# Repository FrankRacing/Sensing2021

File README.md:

# Olin Baja Electrical 2021

This repository contains the hardware, firmware, software, and important technical documents for the 2021 iteration of Olin College of Engineering's Baja project team.

## Repository structure

- hardware: boards 
- packages: store
- parts: COTs 

## Instructions to commit:

The main branch is protected, so you cannot commit directly! You need to make a branch first. We suggest learning how to use VSCode's Version Control tab and installing the GitLens extension.

- Make sure your main branch is up to date (git pull)
- Make sure you're on the main branch
- Call `git checkout -b <your initials>/<branch_name>` 
  - IE for me it would be `git checkout -b jk/important_feature`
- Work on your code, committing frequently
- Push your code to Github
- Make a pull request with your branch
- Wait for your code to be reviewed, responding to review requests
- Merge your branch, and then delete it.

This process will need to be repeated for every change you want to make to the main repository

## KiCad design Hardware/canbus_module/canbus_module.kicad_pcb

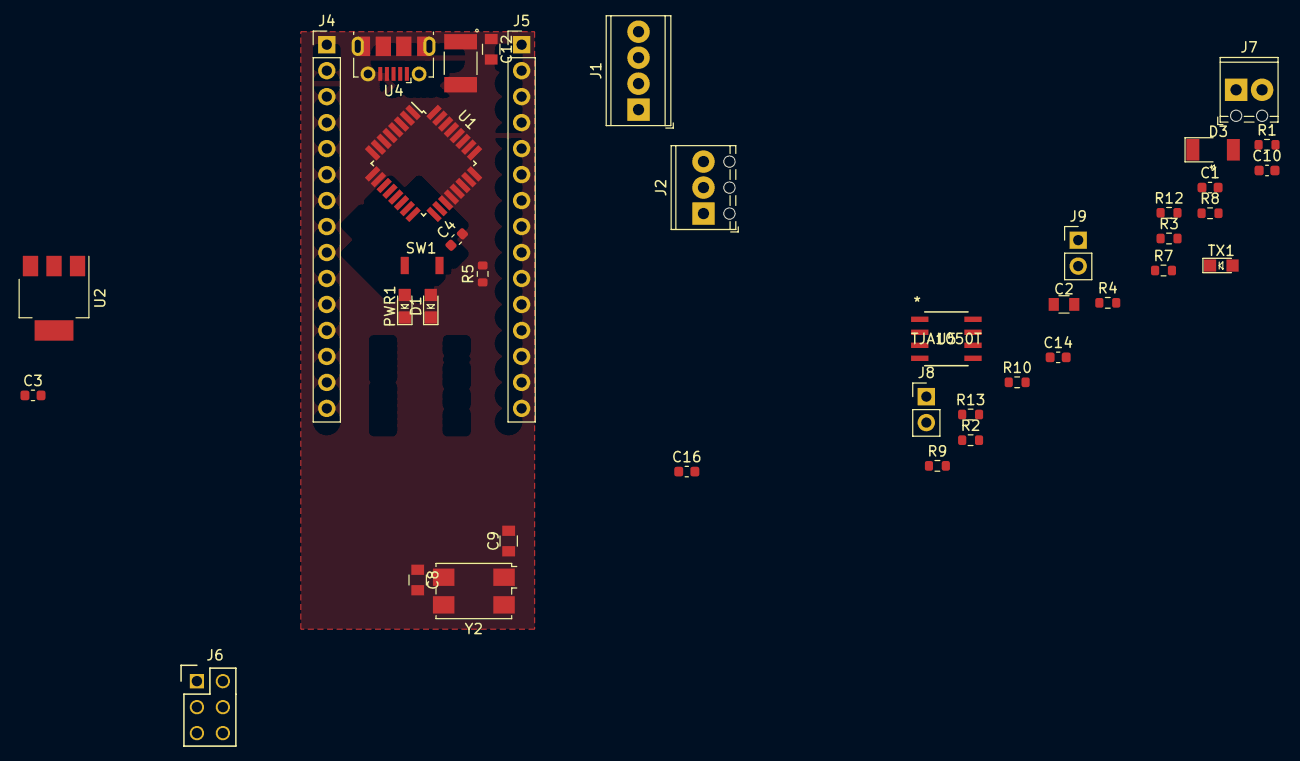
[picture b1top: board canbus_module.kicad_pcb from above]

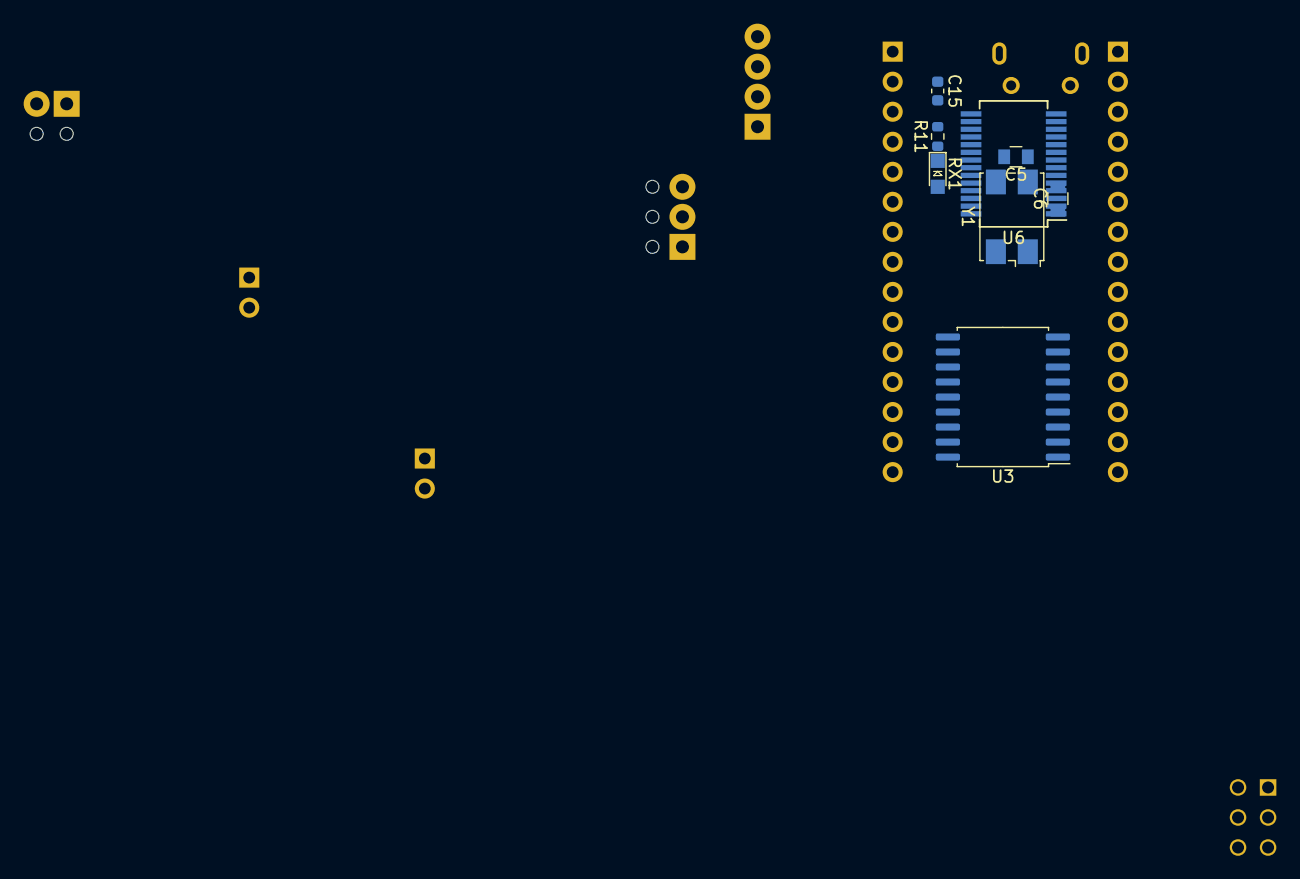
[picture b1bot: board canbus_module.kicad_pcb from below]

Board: 2 copper layers, 48 parts (8 on the bottom side), 50 nets, no tracks yet.

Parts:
C1, C3, C4, C14, C15, C16: C_100nF; C_0603_1608Metric
C2, C12: C_4.7uF_25V; C_0805_OEM
C5, C6, C8, C9: C_30pF; C_0805_OEM
C10: 1uF; C_0603_1608Metric
D1: LED_0805; LED_0805_OEM
D3: DIODE; D_5.6V_Zener
F1: Polyfuse; FUSM4632X85
J1: Screw_Terminal_01x04; TerminalBlock_Phoenix_MPT-0,5-4-2.54_1x04_P2.54mm_Horizontal
J2: Screw_Terminal_01x03; TerminalBlock_Phoenix_MPT-0,5-3-2.54_1x03_P2.54mm_Horizontal
J4, J5: Conn_01x15_Male; PinHeader_1x15_P2.54mm_Vertical
J6: CONN_02X03; Pin_Header_Straight_2x03
J7: TB002-500-02BE; TerminalBlock_Phoenix_MPT-0,5-2-2.54_1x02_P2.54mm_Horizontal
J8, J9: Conn_01x02; PinHeader_1x02_P2.54mm_Vertical
PWR1: LED_0805; LED_0805_OEM
R1, R2, R3, R4, R5, R7, R8, R9, R11, R12: 1k; R_0603_1608Metric
R10: 10k; R_0603_1608Metric
R13: 120; R_0603_1608Metric
RX1: LED_0805; LED_0805_OEM
SW1: SW_Push_SPST_NO; SW_B3U-1000P_4.2x1.7mm
TX1: LED_0805; LED_0805_OEM
U1: ATmega328P-AU; TQFP-32_7x7mm_P0.8mm
U2: LM1117-ADJ; SOT-223
U3: MCP2515-xSO; SOIC-18W_7.5x11.6mm_P1.27mm
U4: USB_MicroB; USB_Micro-B_Molex-105017-0001
U5: TJA1050T
U6: FT232RL; SSOP-28_5.3x10.2mm_P0.65mm
Y1, Y2: Crystal; Crystal_SMD_7050-4Pin_7.0x5.0mm

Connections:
+3V3: C15.1, J5.14, U6.17
+5V: C1.2, C2.1, C3.2, C10.1, C16.2, D3.2, J1.1, J2.1, J4.3, J5.3, J5.4, J6.2, J6.5, R1.1, R2.1, R7.1, R9.2, R10.1, RX1.2, TX1.2, U1.4, U1.18, U1.29, U2.2, U3.18, U5.3, U6.4, U6.20
/A0: J5.12, U1.23
/A1: J5.11, U1.24
/A2: J2.2, J5.10, U1.25
/A3: J5.9, U1.26
/A4: J5.8, U1.27
/A5: J5.7, U1.28
/A7: J5.5, U1.22
/CS: J4.13, U1.14, U3.16
/D2: J4.5, U1.32
/D3: J1.2, J4.6, R2.2, U1.1
/D4: J1.3, J4.7, R1.2, U1.2
/D5: J4.8, U1.9
/D6: J4.9, U1.10
/D7: J4.10, U1.11
/D8: J4.11, U1.12
/D9: J4.12, U1.13
/RX: J4.2, R3.2, U6.5
/RXCAN: U3.2, U5.4
/SCK: J5.15, J6.3, R5.2, U1.17, U3.13
/SI: J4.14, J6.4, U1.15, U3.14
/SO: J4.15, J6.1, U1.16, U3.15
/TX: J4.1, R4.2, U6.1
/TXCAN: U3.1, U5.1
/VIN: J5.1, U2.3
/VUSB: C12.1, C14.2, D3.1, F1.1
GND: C1.1, C2.2, C3.1, C4.1, C5.1, C6.1, C8.2, C9.2, C10.2, C12.2, C14.1, C15.2, D1.1, J1.4, J2.3, J4.4, J5.2, J6.6, PWR1.1, R8.1, R8.2, SW1.1, U1.3, U1.5, U1.6, U1.21, U2.1, U3.9, U4.5, U4.6, U5.2, U5.8, U6.7, U6.18, U6.21, U6.25, U6.26
unnamed: C4.2, U1.20
unnamed: C5.2, U1.7, Y1.2
unnamed: C6.2, U1.8, Y1.1
unnamed: C8.1, U3.7, Y2.2
unnamed: C9.1, U3.8, Y2.1
unnamed: C16.1, U6.2
unnamed: D1.2, R5.1
unnamed: F1.2, U4.1
unnamed: J7.1, J9.1, R13.1, U5.7
unnamed: J7.2, J8.2, J9.2, U5.6
unnamed: J8.1, R13.2
unnamed: PWR1.2, R9.1
unnamed: R3.1, U1.30
unnamed: R4.1, U1.31
unnamed: R7.2, SW1.2
unnamed: R10.2, U3.17
unnamed: R11.1, RX1.1
unnamed: R11.2, U6.23
unnamed: R12.1, TX1.1
unnamed: R12.2, U6.22
unnamed: U4.2, U6.16
unnamed: U4.3, U6.15

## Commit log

2021-09-28 Added canbus_module to git.
    Unsure if connecters J8 & J9 are necessary. They exist on the
    commercial CANbus module. Also, wanted to check if capacitors are
    okay position-wise as well as how to do the clock routing.
2021-09-29 feat: add parts repo
2021-09-29 feat: use our fork
2021-09-29 chore: setup repository
2021-09-29 feat: add a package
2021-09-29 chore: add instructions on how to commit
2021-10-29 wip: add bthost

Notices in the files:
parts and their libraries:
Copyright 2016 Accelerated Designs. All rights reserved.
